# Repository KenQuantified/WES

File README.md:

# WES
Wireless Environment Sensor

This project is for a wireless environment sensor design build and software development. This project includes the following elements:
System Design (Enterprise Architect Model)
Electronic Design and PCB Layout
Software Development (Assembly Code)

Please note, this project is not complete and does not work. It has been abandoned due to cost.

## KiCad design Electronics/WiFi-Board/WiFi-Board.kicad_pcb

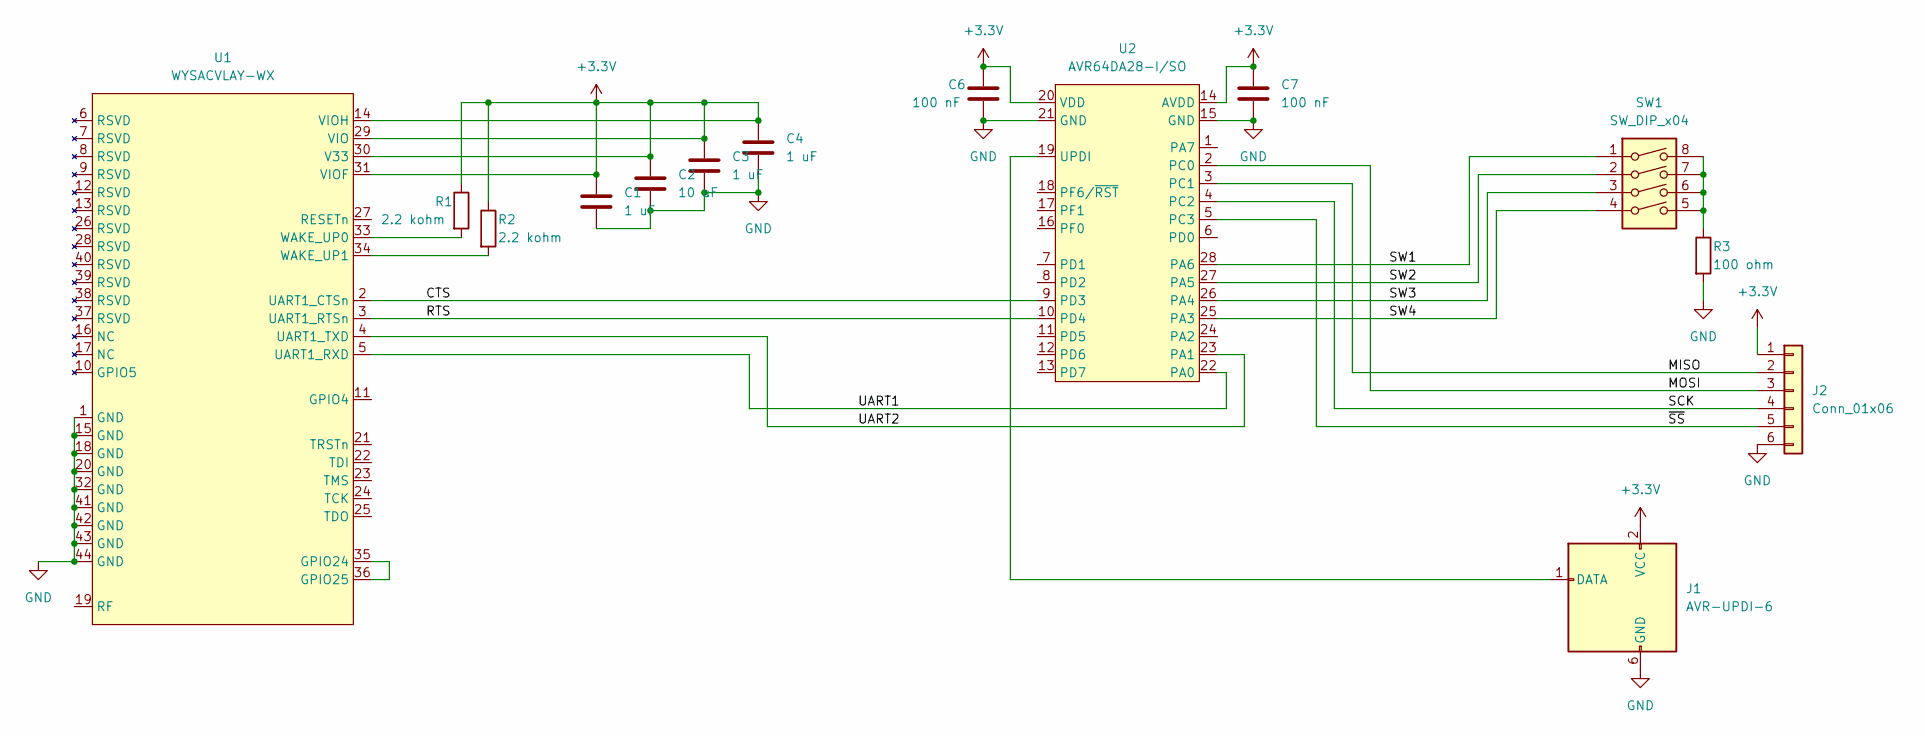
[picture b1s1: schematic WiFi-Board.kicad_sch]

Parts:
C1, C3, C4: 1 uF; C_0805_2012Metric
C2: 10 uF; C_0805_2012Metric
C6, C7: 100 nF; C_0805_2012Metric
J1: AVR-UPDI-6; PinHeader_2x03_P2.54mm_Vertical
J2: Conn_01x06; PinSocket_1x06_P2.54mm_Vertical
R1, R2: 2.2 kohm; R_0805_2012Metric
R3: 100 ohm; R_0805_2012Metric
SW1: SW_DIP_x04; DIP-8_W7.62mm_Socket
U1: WYSACVLAY-WX
U2: AVR64DA28-I/SO; SOIC-28W_7.5x17.9mm_P1.27mm

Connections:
+3V3: C1.1, C2.1, C3.1, C4.1, C6.1, C7.1, J1.2 (VCC), J2.1, R1.1, R2.1, U1.14 (VIOH), U1.29 (VIO), U1.30 (V33), U1.31 (VIOF), U2.14 (AVDD), U2.20 (VDD)
/CTS: U1.2 (UART1_CTSn), U2.9 (PD3)
/MISO: J2.2, U2.3 (PC1)
/MOSI: J2.3, U2.2 (PC0)
/RTS: U1.3 (UART1_RTSn), U2.10 (PD4)
/SCK: J2.4, U2.4 (PC2)
/SW1: SW1.1, U2.28 (PA6)
/SW2: SW1.2, U2.27 (PA5)
/SW3: SW1.3, U2.26 (PA4)
/SW4: SW1.4, U2.25 (PA3)
/UART1: U1.5 (UART1_RXD), U2.22 (PA0)
/UART2: U1.4 (UART1_TXD), U2.23 (PA1)
/~SS: J2.5, U2.5 (PC3)
GND: C1.2, C2.2, C3.2, C4.2, C6.2, C7.2, J1.6 (GND), J2.6, R3.2, U1.1 (GND), U1.15 (GND), U1.18 (GND), U1.20 (GND), U1.32 (GND), U1.41 (GND), U1.42 (GND), U1.43 (GND), U1.44 (GND), U2.15 (GND), U2.21 (GND)
unnamed: J1.1 (DATA), U2.19 (UPDI)
unnamed: R1.2, U1.33 (WAKE_UP0)
unnamed: R2.2, U1.34 (WAKE_UP1)
unnamed: R3.1, SW1.5, SW1.6, SW1.7, SW1.8
unnamed: U1.35 (GPIO24), U1.36 (GPIO25)

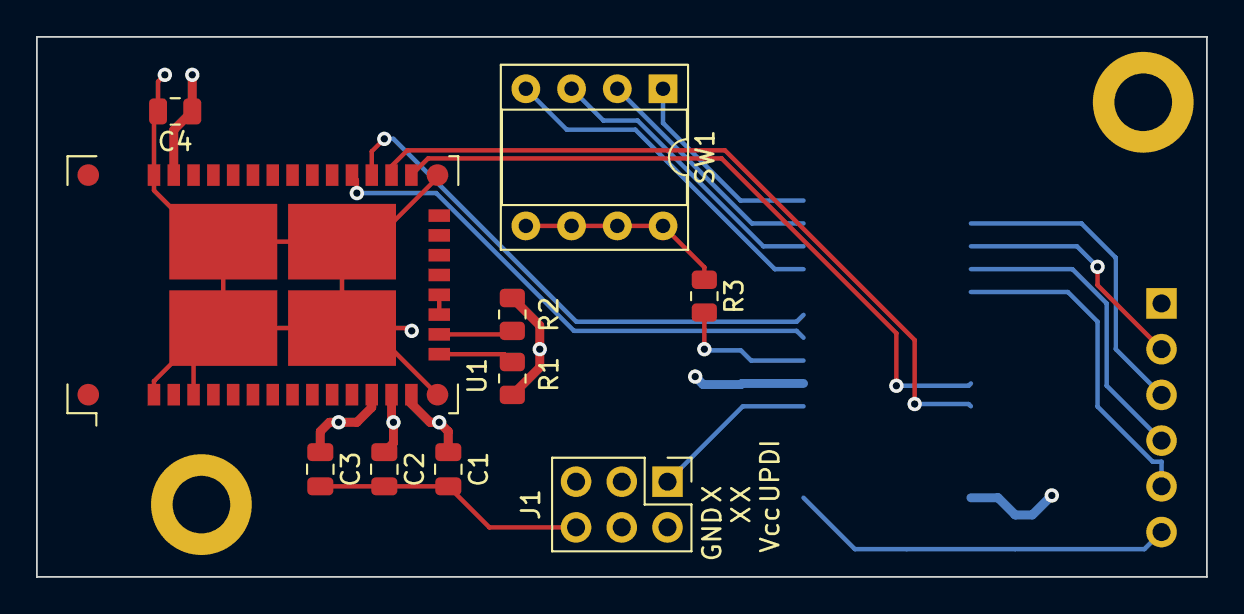
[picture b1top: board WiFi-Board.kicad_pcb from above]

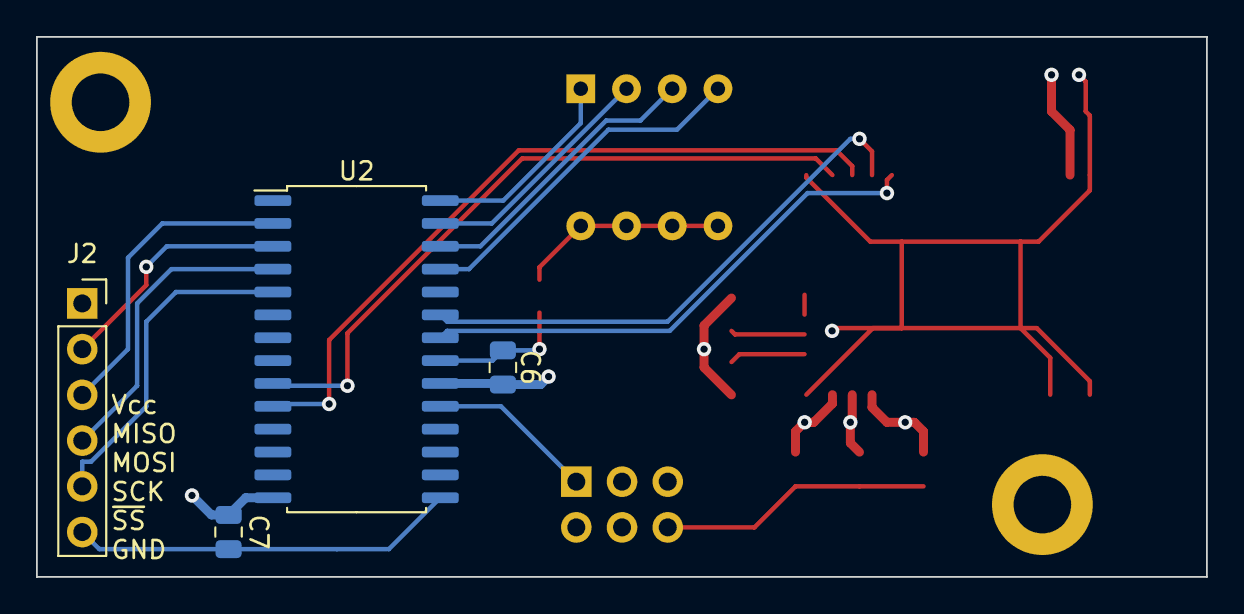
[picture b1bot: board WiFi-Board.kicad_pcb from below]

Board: 4 copper layers, 65.0 x 30.0 mm, 14 parts (4 on the bottom side), 19 nets.

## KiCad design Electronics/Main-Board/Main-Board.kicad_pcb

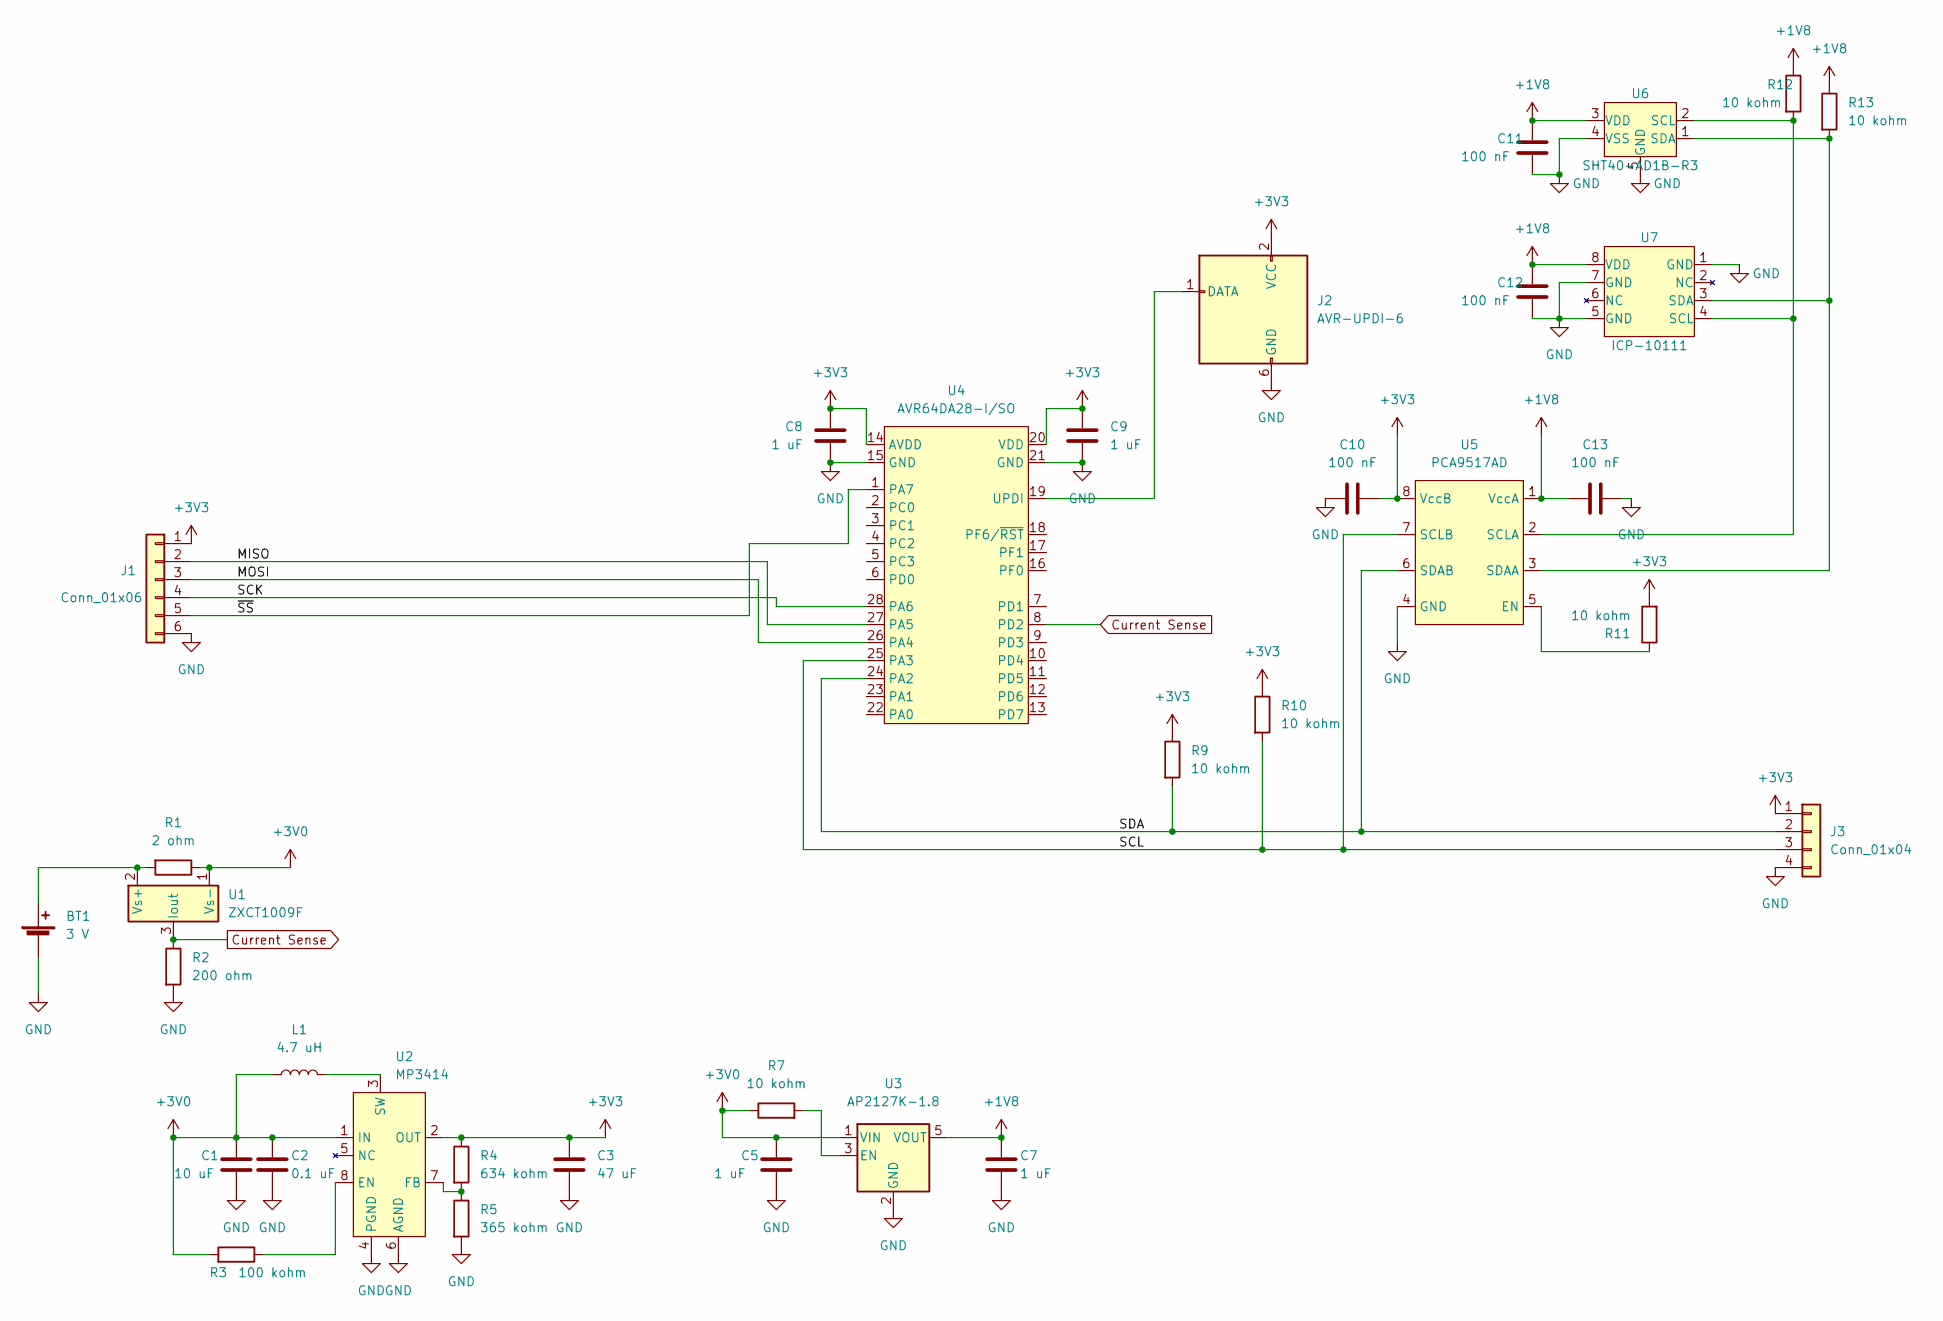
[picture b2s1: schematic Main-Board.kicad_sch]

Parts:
BT1: 3 V; BatteryHolder_Keystone_103_1x20mm
C1: 10 uF; C_0805_2012Metric
C2: 0.1 uF; C_0805_2012Metric
C3: 47 uF; C_0805_2012Metric
C5, C8, C9: 1 uF; C_0805_2012Metric
C7: 1 uF; CP_Radial_D4.0mm_P1.50mm
C10, C11, C12, C13: 100 nF; C_0805_2012Metric
J1: Conn_01x06; PinHeader_1x06_P2.54mm_Vertical
J2: AVR-UPDI-6; PinHeader_2x03_P2.54mm_Vertical
J3: Conn_01x04; PinSocket_1x04_P2.54mm_Vertical
L1: 4.7 uH; L_0805_2012Metric_Pad1.05x1.20mm_HandSolder
R1: 2 ohm; R_0805_2012Metric
R2: 200 ohm; R_0805_2012Metric
R3: 100 kohm; R_0805_2012Metric
R4: 634 kohm; R_0805_2012Metric
R5: 365 kohm; R_0805_2012Metric
R7, R9, R10, R11, R12, R13: 10 kohm; R_0805_2012Metric
U1: ZXCT1009F; SOT-23
U2: MP3414; TSOT-23-8
U3: AP2127K-1.8; SOT-23-5
U4: AVR64DA28-I/SO; SOIC-28W_7.5x17.9mm_P1.27mm
U5: PCA9517AD; SOIC-8_3.9x4.9mm_P1.27mm
U6: SHT40-AD1B-R3; DFN-4-PADS0.5x0.3mm_SP1.4x0.8mm
U7: ICP-10111

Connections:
+1V8: C7.1, C11.1, C12.1, C13.1, R12.1, R13.1, U3.5 (VOUT), U5.1 (VccA), U6.3 (VDD), U7.8 (VDD)
+3V0: C1.1, C2.1, C5.1, L1.2, R1.1, R3.2, R7.1, U1.1 (Vs-), U2.1 (IN), U3.1 (VIN)
+3V3: C3.1, C8.1, C9.2, C10.2, J1.1, J2.2 (VCC), J3.1, R4.1, R9.1, R10.1, R11.2, U2.2 (OUT), U4.14 (AVDD), U4.20 (VDD), U5.8 (VccB)
/MISO: J1.2, U4.27 (PA5)
/MOSI: J1.3, U4.26 (PA4)
/SCK: J1.4, U4.28 (PA6)
/SCL: J3.3, R10.2, U4.25 (PA3), U5.7 (SCLB)
/SDA: J3.2, R9.2, U4.24 (PA2), U5.6 (SDAB)
/~SS: J1.5, U4.1 (PA7)
Current Sense: R2.1, U1.3 (Iout), U4.8 (PD2)
GND: BT1.2 (-), C1.2, C2.2, C3.2, C5.2, C7.2, C8.2, C9.1, C10.1, C11.2, C12.2, C13.2, J1.6, J2.6 (GND), J3.4, R2.2, R5.2, U2.4 (PGND), U2.6 (AGND), U3.2 (GND), U4.15 (GND), U4.21 (GND), U5.4 (GND), U6.4 (VSS), U6.5 (GND), U7.1 (GND), U7.5 (GND), U7.7 (GND)
unnamed: BT1.1 (+), R1.2, U1.2 (Vs+)
unnamed: J2.1 (DATA), U4.19 (UPDI)
unnamed: L1.1, U2.3 (SW)
unnamed: R3.1, U2.8 (EN)
unnamed: R4.2, R5.1, U2.7 (FB)
unnamed: R7.2, U3.3 (EN)
unnamed: R11.1, U5.5 (EN)
unnamed: R12.2, U5.2 (SCLA), U6.2 (SCL), U7.4 (SCL)
unnamed: R13.2, U5.3 (SDAA), U6.1 (SDA), U7.3 (SDA)

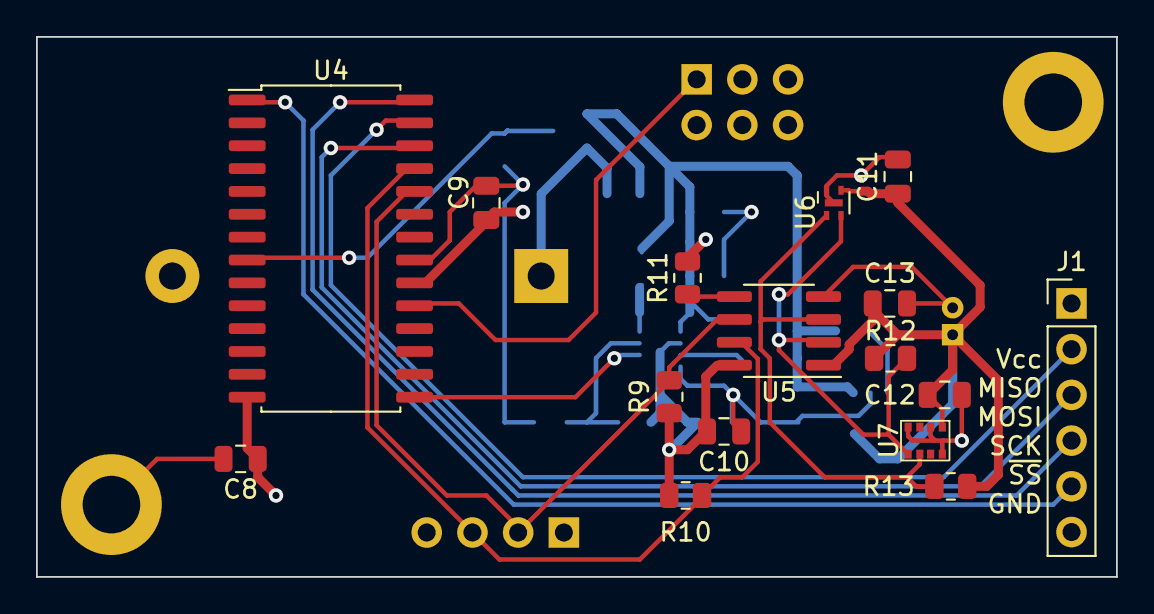
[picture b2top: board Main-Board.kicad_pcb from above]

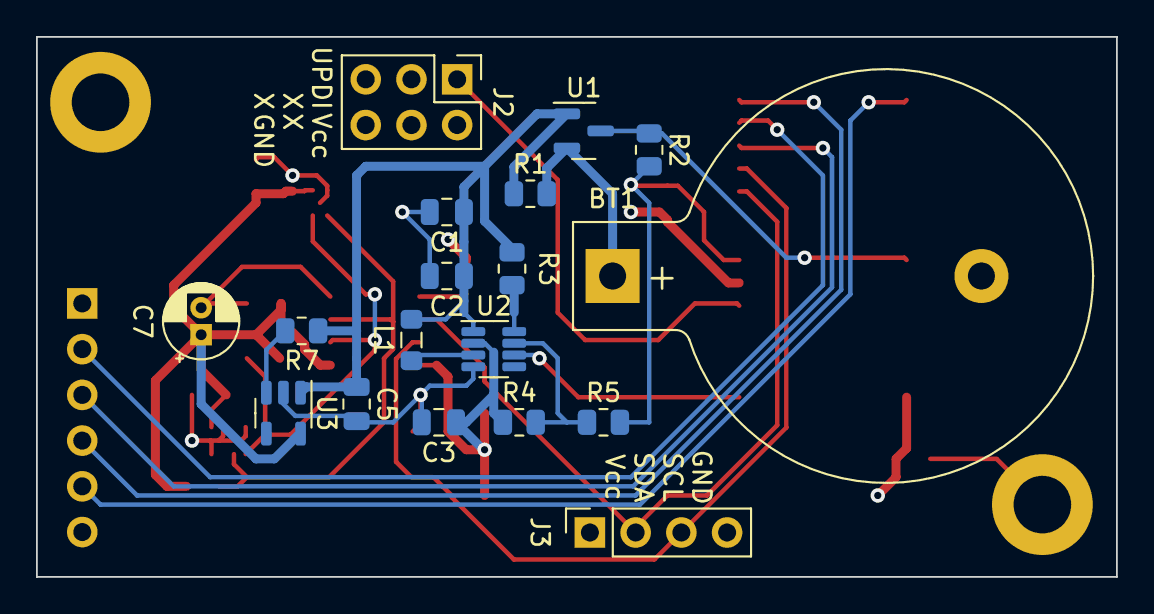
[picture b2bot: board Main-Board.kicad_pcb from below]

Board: 4 copper layers, 60.0 x 30.0 mm, 34 parts (18 on the bottom side), 20 nets.

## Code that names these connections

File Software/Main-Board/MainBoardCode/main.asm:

;
; MainBoardCode.asm
;
; Created: 2022-04-01 7:13:18 PM
; Author : kenqu
;

;define SRAM storage locations for sensor data
.equ TEMP_1 = 0x6000 ;three bytes PT
.equ TEMP_2 = 0x6003 ;three bytes HT
.equ PRESSURE = 0x6006 ;six bytes
.equ HUMIDITY = 0x600D ;three bytes
.equ CURRENT = 0x6011 ;two bytes
.equ PT_Address = 0x63
.equ HT_Address = 0x44

;define SPI data storage locations
.equ SPI_TX = 0x6050
.equ SPI_RX = 0x6060

;setup interrupt vectors
.org 0x0000
rjmp init
.org NMI_vect
reti
.org BOD_VLM_vect
reti
.org RTC_CNT_vect
reti
.org RTC_PIT_vect
reti
.org CCL_CCL_vect
reti
.org PORTA_PORT_vect
reti
.org TCA0_OVF_vect
reti
.org TCA0_HUNF_vect
reti
.org TCA0_LCMP0_vect
reti
.org TCA0_LCMP1_vect
reti
.org TCA0_LCMP2_vect
reti
.org TCB0_INT_vect
reti
.org TCB1_INT_vect
reti
.org TCD0_OVF_vect
reti
.org TCD0_TRIG_vect
reti
.org TWI0_TWIS_vect
reti
.org TWI0_TWIM_vect
rjmp twiinterrupt
.org SPI0_INT_vect
reti
.org USART0_RXC_vect
reti
.org USART0_DRE_vect
reti
.org USART0_TXC_vect
reti
.org PORTD_PORT_vect
reti
.org AC0_AC_vect
reti
.org ADC0_RESRDY_vect
rjmp readadcresult
.org ADC0_WCMP_vect
reti
.org ZCD0_ZCD_vect
reti
.org PTC_PTC_vect
reti
.org AC1_AC_vect
reti
.org PORTC_PORT_vect
reti
.org TCB2_INT_vect
reti
.org USART1_RXC_vect
reti
.org USART1_DRE_vect
reti
.org USART1_TXC_vect
reti
.org PORTF_PORT_vect
reti
.org NVMCTRL_EE_vect
reti
.org SPI1_INT_vect
reti
.org USART2_RXC_vect
reti
.org USART2_DRE_vect
reti
.org USART2_TXC_vect
reti
.org AC2_AC_vect
reti

;initialize controller at start
init:
	;configure PORT A
	ldi r16, 0b00000100 ;disable input
	ldi XH, High(PORTA_PINCONFIG)
	ldi XL, Low(PORTA_PINCONFIG)
	st X, r16
	ldi r16, 0b00000011 ;disable ports PA0 and PA1
	ldi XH, High(PORTA_PINCTRLUPD)
	ldi XL, Low(PORTA_PINCTRLUPD)
	st X, r16
	;PA7 PA6 PA4 PA3 and PA2 are outputs
	ldi r16, 0b11011100
	ldi XH, High(PORTA_DIRSET)
	ldi XL, Low(PORTA_DIRSET)
	st X, r16

	;configure PORT C
	;nothing on PORT C
	ldi r16, 0b11111111
	ldi XH, High(PORTC_PINCTRLUPD)
	ldi XL, Low(PORTC_PINCTRLUPD)
	st X, r16

	;configure PORT D
	;PORT D has the current sensor on PD2 and nothing else.
	ldi r16, 0b11111011 ;disable all except PD2
	ldi XH, High(PORTD_PINCTRLUPD)
	ldi XL, Low(PORTD_PINCTRLUPD)
	st X, r16

	;configure PORT F
	;nothing on PORT F
	ldi r16, 0b11111111 ;disable all
	ldi XH, High(PORTF_PINCTRLUPD)
	ldi XL, Low(PORTF_PINCTRLUPD)
	st X, r16

	;configure ADC
	;Configure CTRLA
	ldi r16, 0b00000000 ;stby off, single ended, RA, 12-bit, on-command, disabled (for now)
	ldi XH, High(ADC0_CTRLA)
	ldi XL, Low(ADC0_CTRLA)
	st X, r16
	;CTRLB is default, no accumulation
	;Configure CTRLC
	ldi r16, 0x0D ;slow down the clock, divide by 256 for ADC
	ldi XH, High(ADC0_CTRLC)
	ldi XL, Low(ADC0_CTRLC)
	st X, r16
	;CTRLD is default, no delay in init or sampling
	;CTRLE is default, no window comparison
	;SAMPCTRL is default
	;PD2 is AIN2
	ldi r16, 0x02 ;Set AIN2 to the ADC +input
	ldi XH, High(ADC0_MUXPOS)
	ldi XL, Low(ADC0_MUXPOS)
	st X, r16
	ldi r16, 0x40 ;Set GND to the ADC -input
	ldi XH, High(ADC0_MUXNEG)
	ldi XL, Low(ADC0_MUXNEG)
	st X, r16
	;enable debug mode
	ldi r16, 0x01
	ldi XH, High(ADC0_DBGCTRL)
	ldi XL, Low(ADC0_DBGCTRL)
	st X, r16
	;enable result interrupt
	ldi r16, 0x01 ;set the result interrupt on
	ldi XH, High(ADC0_INTCTRL)
	ldi XL, Low(ADC0_INTCTRL)
	st X, r16
	;Enable ADC
	ldi r16, 0b00000001 ;stby off, single ended, RA, 12-bit, on-command, Enable
	ldi XH, High(ADC0_CTRLA)
	ldi XL, Low(ADC0_CTRLA)
	st X, r16

	;configure TWI(I2C)
	;setup SDASETUP and SDAHOLD in CTRLA
	ldi r16, 0b00000000 ;i2c mode, 4cycle SDA Setup, no SDA Hold, FM+ Disabled
	ldi XH, High(TWI0_CTRLA)
	ldi XL, Low(TWI0_CTRLA)
	st X, r16
	;enable debug mode
	ldi r16, 0x01
	ldi XH, High(TWI0_DBGCTRL)
	ldi XL, Low(TWI0_DBGCTRL)
	st X, r16
	;set MBAUD ;400 kHz, SM/FM/FM+, BAUD of 2 should be okay?
	ldi r16, 0x02
	ldi XH, High(TWI0_MBAUD)
	ldi XL, Low(TWI0_MBAUD)
	st X, r16

	sei
	rjmp runloop

runloop:
	rjmp runloop

enabletwi:
	;enable r/w interrupts and master
	cli
	ldi r16, 0b11000001 ;interrupts on, QC off, timeout off, SM disabled, Enable master
	ldi XH, High(TWI0_MCTRLA)
	ldi XL, Low(TWI0_MCTRLA)
	st X, r16
	;Idle the bus (set MSTATUS BUSSTATE to 0x01)
	ldi r16, 0b00000001
	ldi XH, High(TWI0_MSTATUS)
	ldi XL, Low(TWI0_MSTATUS)
	st X, r16
	sei

	ret
    
disabletwi:
	cli
	ldi r16, 0b00000000 ;interrupts off, QC off, timeout off, SM disabled, disable master
	ldi XH, High(TWI0_MCTRLA)
	ldi XL, Low(TWI0_MCTRLA)
	st X, r16
	sei

	ret

twiinterrupt:
	cli
	ldi XH, High(TWI0_MSTATUS)
	ldi XL, Low(TWI0_MSTATUS)
	ld r17, X
	sbrc r17, 7
	call readtwi
	sbrc r17, 6
	call writetwi
	sei

	reti

readtwi:
	ldi XH, High(TWI0_MDATA)
	ldi XL, Low(TWI0_MDATA)
	ld r16, X

	ret

writetwi:
	ldi r16, 0xFD
	ldi XH, High(TWI0_MDATA)
	ldi XL, Low(TWI0_MDATA)
	ld r16, X
	
	ret

runadc:
	ldi r16, 0x01 ;start conversion
	ldi XH, High(ADC0_COMMAND)
	ldi XL, Low(ADC0_COMMAND)
	st X, r16

	ret

readadcresult:
	push r16
	push XH
	push XL

	;read results to SRAM
	ldi XH, High(ADC0_RESL)
	ldi XL, Low(ADC0_RESL)
	ld r16, X
	ldi XH, High(ADC0_RESH)
	ldi XL, Low(ADC0_RESH)
	ld r17, X
	ldi XH, High(CURRENT)
	ldi XL, Low(CURRENT)
	st X+, r17
	st X, r16

	pop XL
	pop XH
	pop r16

	reti
